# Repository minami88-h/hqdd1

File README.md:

# HQDD1 — 小型 QDD(準ダイレクトドライブ)アクチュエータ

ジンバルモーター(2204 / 260KV)+ 減速機を、自作の制御基板 **hqdd_1** で駆動する QDD アクチュエータの、基板設計・ファームウェア・操作用 Web UI をまとめたリポジトリです。

*A small quasi-direct-drive actuator: a custom STM32G431 + DRV8311H FOC driver board (KiCad files included), SimpleFOC-based firmware with CAN/UART control, and a browser UI (Web Serial / SocketCAN). Documentation is mostly in Japanese.*

| | |
|---|---|
| MCU | STM32G431KBUx(UFQFPN32、128 KB flash / 32 KB RAM) |
| モータードライバ | TI DRV8311H(3 × PWM、低サイド電流センス) |
| 角度センサー | AS5600L(I2C、12 bit) |
| CAN トランシーバ | TCAN330(FDCAN1、1 Mbps) |
| モーター | ジンバル 2204-260KV(極対数 7)、減速比 29.16 または 5.4 |
| 制御 | SimpleFOC による電流 FOC(トルク / 速度 / 位置モード) |
| 入力電圧 | LiPo バッテリー(2 セル直列 = 2S で動作確認)。3 セル直列(3S)は、UI で電源電圧を 12 V に設定すれば使える想定(実機では未確認) |

## 構成

```
hqdd1/
├── firmware/   PlatformIO プロジェクト(STM32G431 + SimpleFOC、CAN/UART 通信)
├── webui/      操作用 Web UI(ブラウザ + 任意のバックエンド server.py)
├── hardware/   KiCad プロジェクト(回路図・PCB・3D モデル・製造データ)
└── docs/       通信仕様書(Markdown / PDF)、アクチュエータの仕様サマリー
```

## 主な機能

- **電流 FOC** — トルク(電流)/ 速度 / 位置の 3 モード。モード切替時は目標を自動で安全な値にする(位置モードは現在位置で保持)。
- **CAN(FDCAN1)と UART の両方で制御** — 同じコマンド文字列を使います。CAN は最大 8 台を同一バスに接続でき、UART も `@<ID>` で宛先を指定できます。仕様は [docs/communication_spec.md](docs/communication_spec.md)([PDF](docs/communication_spec.pdf))。
- **パラメータの調整・保存** — PID ゲイン、電流/速度/電圧の上限、電源電圧、減速比を通信経由で変更でき、フラッシュに保存して電源を切っても保持。出荷状態(コード上の値)へ戻すコマンドもあります。
- **Web UI** — リアルタイムグラフ(項目を選んで増やせる)、運転操作、PID・制限値の調整、高速キャプチャ(ステップ応答の記録)。
- **ボタンとLED** — 基板上のボタンでデバイス ID を設定し、LED で ID と負荷を表示。

## はじめに

### 1. ファームウェアを書き込む

必要なもの: [PlatformIO](https://platformio.org/)、ST-Link(基板に ST-Link は載っていないので、J2 の SWDIO/SWCLK に外付けします)。

```bash
cd firmware
pio run                 # ビルド
pio run -t upload       # ST-Link で書き込み
```

> **新しい基板に初めて書き込むときは、先に下の「オプションバイトの修正」を一度だけ実行してください。** しないと、書き込みは成功しても毎回ブートローダに入り、動きません。

**書き込みの動作について。** ビルドごとに固有の番号を保存データに付けているため、**プログラムを書き込み直すと、保存済みのパラメータとデバイス ID はコード上の値に戻ります**。調整した値を残したい場合は、コードの初期値(`firmware/src/main.cpp`)に反映してから書き込んでください。ID の既定値は `firmware/src/device_id.h` の `DEFAULT_DEVICE_ID` です。

### 2. 配線

| 機能 | 内容 |
|---|---|
| 電源 | LiPo バッテリー。2 セル直列(2S、公称 7.4 V)で動作確認。UI の「電源電圧」を 2S = 8 V / 3S(3 セル直列、公称 11.1 V)= 12 V に合わせる。3S は実機未確認で、電源まわりの部品の耐圧は各自で確認すること |
| UART(J3) | USB-TTL アダプタの TXD → 基板 PA15、RXD → 基板 PA2、GND(3.3 V TTL、115200 bps) |
| CAN | CAN_H / CAN_L、バスの両端に 120 Ω の終端(1 Mbps) |
| 書き込み(J2) | ST-Link の SWDIO / SWCLK / GND |

### 3. Web UI を使う

**UART だけなら、サーバ不要でブラウザだけで使えます。** Chrome または Edge で UI を開き、「接続」を押してシリアルポートを選びます(Web Serial を使うため、Firefox / Safari は非対応)。

- 公開ページ: <https://minami88-h.github.io/hqdd1/>(GitHub Pages)
- ローカルで開く場合: `cd webui/static && python3 -m http.server 8099` → <http://localhost:8099>

**CAN を使う場合**は、PC 側のバックエンドが必要です(Linux の SocketCAN を使います)。

```bash
# CAN アダプタを can0 として立ち上げる(例: gs_usb 系)
sudo ip link set can0 up type can bitrate 1000000
# slcan ファームのアダプタの場合: sudo slcand -o -c -s8 /dev/ttyACM0 can0 && sudo ip link set can0 up

pip install aiohttp pyserial
python3 webui/server.py          # -> http://localhost:8080
```

UART もサーバ経由で使えます(UI のヘッダーで「経路」を切り替え)。

## 通信

CAN と UART の仕様(フレーム形式、コマンド一覧、パラメータ表、複数台の運用)は **[docs/communication_spec.md](docs/communication_spec.md)** にまとめています。簡単な例:

```bash
cansend can0 101#4D4331      # ID=1 に "MC1"(速度モード)
cansend can0 101#4D32        # "M2"(2 rad/s)
candump can0                 # 0x201 に 20 ms 周期でテレメトリ
```

```
@1 MC1                       # UART: ID=1 を速度モードに
@1 M2                        # 2 rad/s
@1 ?VP                       # -> #1 GAIN VP 0.03000
```

## ハードウェア

KiCad のプロジェクトは [hardware/](hardware/) にあります(KiCad 10 で保存。4 層基板)。製造用データ(ガーバー、BOM、実装位置)は `hardware/production/` です。詳しくは [hardware/README.md](hardware/README.md)。

### ピン対応

回路図(`hardware/mcu.kicad_sch`)から確定したものです。

| 機能 | MCU ピン | 備考 |
|---|---|---|
| PWM A/B/C → DRV8311 INHA/B/C | PA8 / PA9 / PA10 | TIM1 CH1/2/3 |
| DRV8311 nSLEEP(enable) | PB0 | アクティブ High |
| 電流センス SOA / SOB | PA0 / PA1 | ADC1。GAIN は 3.3 V 直結(2 V/A) |
| AS5600L I2C | SDA = PB7、SCL = PB8 | I2C1(AF4) |
| デバッグ UART(USART2) | TX = PA2、RX = PA15 | J3 |
| CAN(FDCAN1) | TX = PA12、RX = PA11 | TCAN330 経由 |
| SWD | PA13 / PA14 | J2 |
| LED0 / LED1 | PA4 / PA5 | 負荷検出 / ID 表示 |
| SET_ID(ボタン) | PA3 | 2 秒長押しで ID 設定モード |

回路図のネット名 `UART_TX` = PA15、`UART_RX` = PA2 は、外部機器から見た向きの名前です(MCU から見ると PA2 が送信、PA15 が受信)。**配線は回路図のラベル通り**(アダプタの TXD → `UART_TX`、RXD → `UART_RX`)で動作します。

## 重要な注意点

### オプションバイトの修正(チップごとに 1 回だけ)

STM32G431 は、出荷設定(`nSWBOOT0 = 1`)だと BOOT0 を **PB8 ピンの電圧**で判定します。この基板は PB8 を AS5600 の I2C SCL に使い、4.7 kΩ で 3.3 V にプルアップしているため、**リセットのたびに BOOT0 = High と判定され、毎回システムブートローダに入ってしまいます**(書き込み・ベリファイ自体は成功します)。`nSWBOOT0` をクリアして、常にメインフラッシュから起動するようにします。新品のチップ、または基板を新規製作したときに、ST-Link で 1 回だけ実行してください。

```bash
OOCD=~/.platformio/packages/tool-openocd/bin/openocd
SCRIPTS=~/.platformio/packages/tool-openocd/openocd/scripts
$OOCD -s $SCRIPTS -f interface/stlink.cfg -f target/stm32g4x.cfg \
  -c "init" -c "halt" \
  -c "stm32l4x option_write 0 0x20 0x00000000 0x04000000" \
  -c "stm32l4x option_load 0" \
  -c "shutdown"
```

`option_load` でリセットがかかるため "option load failed" と表示されることがありますが、正常です。設定はチップに恒久保存されます。

### デバッグ用シリアルのピン指定

`firmware/platformio.ini` で `PIN_SERIAL_TX=PA2_ALT1` を指定しています。素の `PA2` だと、STM32duino のピンマップ上で LPUART1 の TX に解決され、USART2 の RX(PA15)と食い違って `Serial` が応答しなくなります。

### 電源電圧の設定

基板には電源電圧を測る回路がありません。LiPo バッテリーを替えたら(2 セル = 2S ⇔ 3 セル = 3S)、UI の「電源電圧」を合わせてください(2S = 8 V、3S = 12 V)。ゲインの変更は不要です。合っていないと電流ループの実効ゲインがずれ、発振することがあります。

### 通信が途切れたときの動作

基板は通信断を検出して停止する機能を持ちません。最後に受けた指令のまま動き続けます。上位側で、定期的な送信と停止手順を用意してください。

## 既知の課題

- **TCAN330 の STANDBY(S)/SHDN ピン**が、基板パターンでは未接続です。現在の実機ではジャンパ線で対処しています(基板の修正が必要です)。
- **DRV8311 の AGND/PGND に接続されているネット名が `VDD`** になっています(`power.kicad_sch` の電源レールと同名)。GND であるべき箇所と思われますが、実害がないため未検証です。基板実体の配線を確認してください。
- CAN の受信はメインループ 1 周につき 1 フレームです(約 2 kHz)。連続して送る場合は 1 ms 以上の間隔を空けてください。

## ライセンス

**非商用であれば自由に使えます。商用利用は、著作権者以外には許可していません。**

| 対象 | ライセンス |
|---|---|
| ソフトウェア(`firmware/`、`webui/` など) | [PolyForm Noncommercial 1.0.0](LICENSES/PolyForm-Noncommercial-1.0.0.md) |
| ハードウェア設計・文書(`hardware/`、`docs/`) | [CC BY-NC 4.0](LICENSES/CC-BY-NC-4.0.txt) |
| `firmware/src/can_driver/` | [ACANFD_STM32](https://github.com/pierremolinaro/ACANFD_STM32)(MIT)。同ディレクトリの `LICENSE-ACANFD_STM32` |

個人・趣味・学習・教育・研究での利用や改変は自由です。商用利用を希望する場合は、[GitHub の Issues](https://github.com/minami88-h/hqdd1/issues) から連絡してください。詳しくは [LICENSE](LICENSE) を参照してください。ビルド時に取得される [SimpleFOC](https://simplefoc.com/) などのライブラリは、それぞれのライセンスに従います。

## 謝辞

[SimpleFOC](https://simplefoc.com/)、[ACANFD_STM32](https://github.com/pierremolinaro/ACANFD_STM32)

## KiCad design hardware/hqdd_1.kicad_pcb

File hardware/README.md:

# hqdd_1 基板(KiCad)

STM32G431KBUx + DRV8311H + AS5600L + TCAN330 の制御基板です。KiCad 10 で保存されています(4 層基板)。古い版では開けません。

## ファイル

| ファイル | 内容 |
|---|---|
| `hqdd_1.kicad_pro` | プロジェクト |
| `hqdd_1.kicad_sch` | ルートの回路図(`mcu` と `power` の 2 シートを持つ) |
| `mcu.kicad_sch` | MCU、DRV8311H、AS5600L、TCAN330、コネクタ類 |
| `power.kicad_sch` | 電源まわり |
| `hqdd_1.kicad_pcb` | PCB |
| `hqdd_1.step` | 3D モデル(PCB から出力) |
| `production/` | 製造用データ(下記) |
| `fabrication-toolkit-options.json` | Fabrication Toolkit(KiCad プラグイン)の出力設定 |

### `production/`

Fabrication Toolkit で出力した発注用データです。

| ファイル | 内容 |
|---|---|
| `hqdd_1.zip` | ガーバーとドリルデータ |
| `bom.csv` | 部品表 |
| `positions.csv` | 部品の実装位置 |
| `designators.csv` | リファレンス一覧 |
| `netlist.ipc` | IPC ネットリスト |

## 既知の課題

- TCAN330 の STANDBY(S)/SHDN ピンが基板パターンで未接続です(ジャンパ線で対処)。
- DRV8311 の AGND/PGND に接続されているネット名が `VDD` になっています。GND であるべき箇所と思われますが、未検証です。

回路の詳細、ピン対応、通信は、ルートの [README](../README.md) を参照してください。

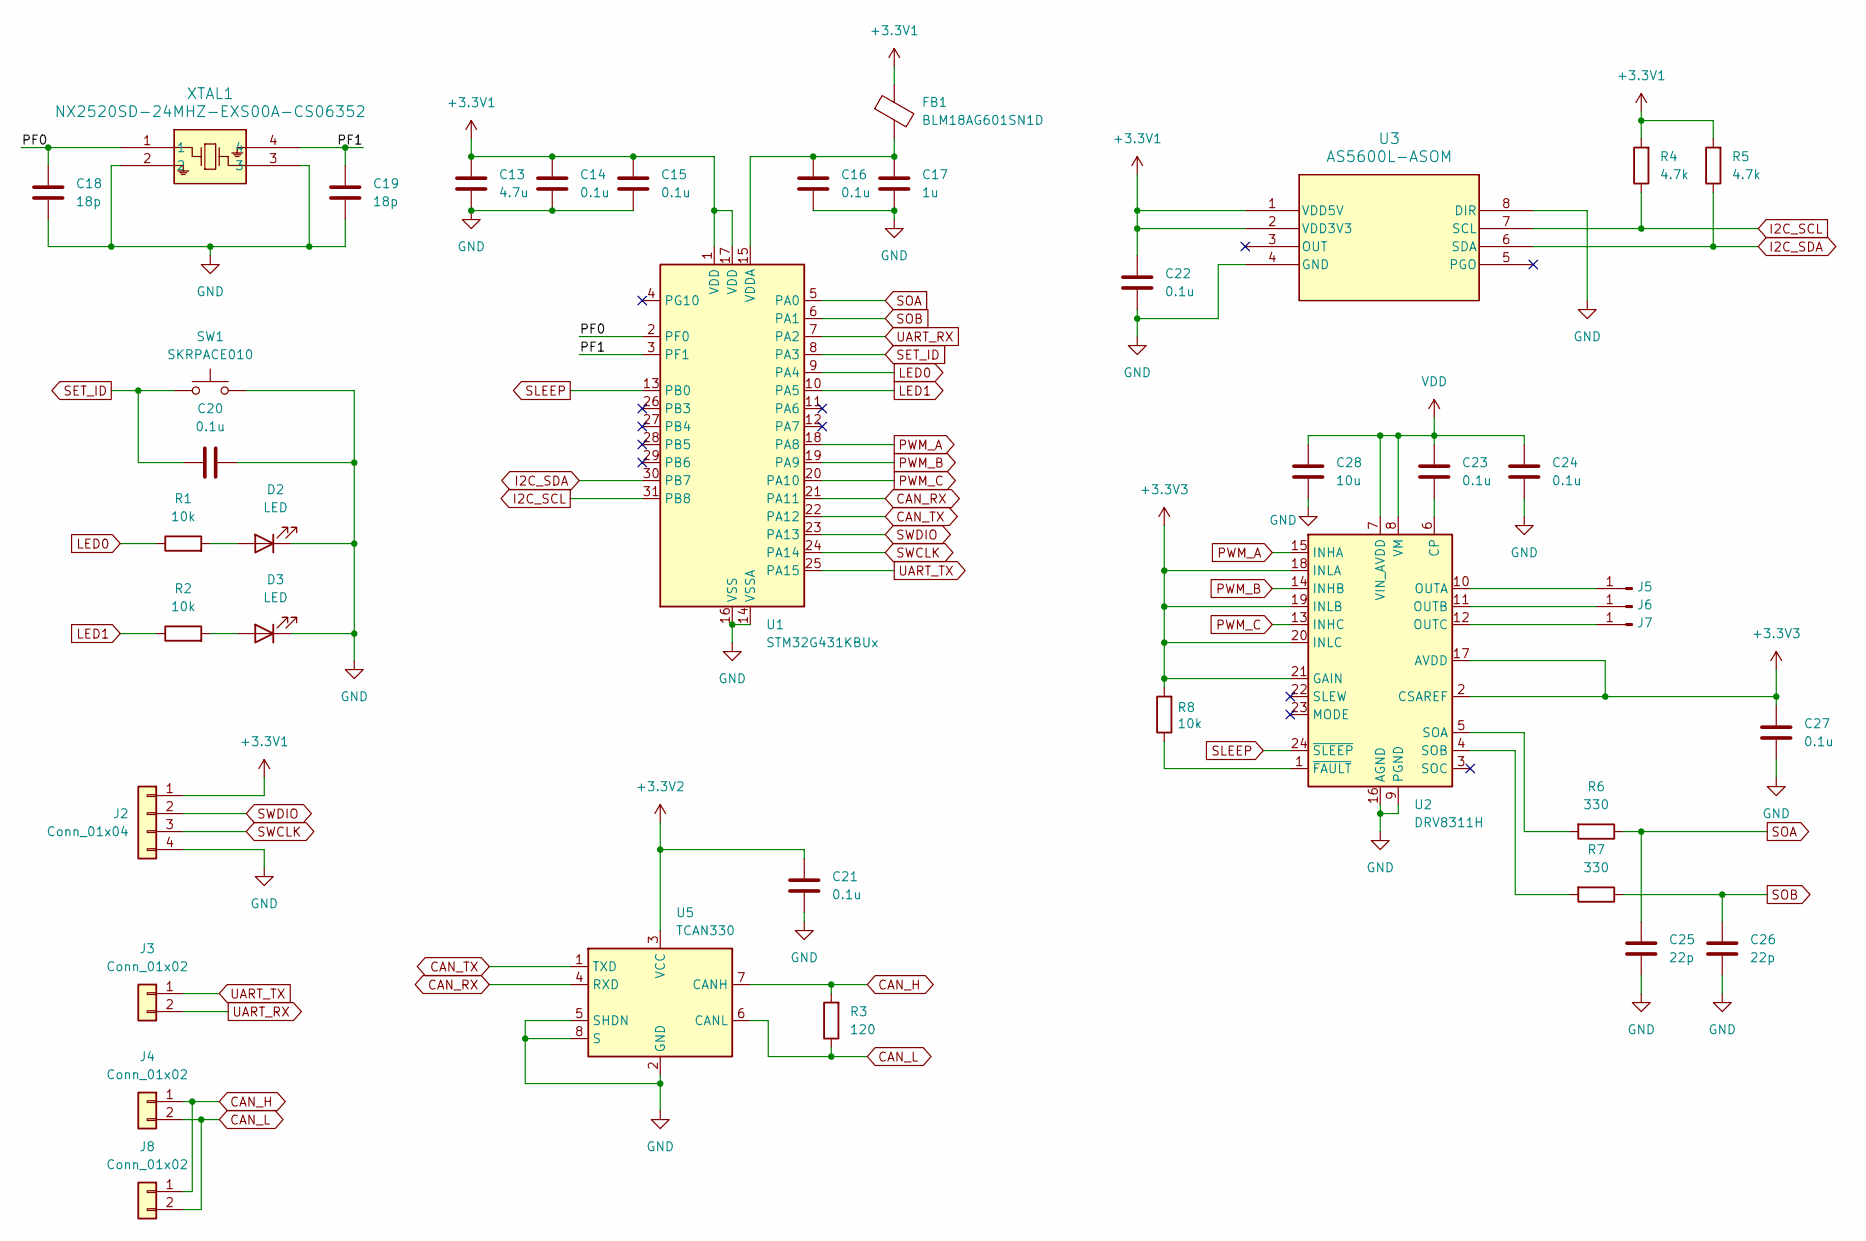
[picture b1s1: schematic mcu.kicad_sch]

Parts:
C13: 4.7u; C_0603_1608Metric_Pad1.08x0.95mm_HandSolder
C14, C15, C16, C20, C21, C22, C23, C24, C27: 0.1u; C_0603_1608Metric_Pad1.08x0.95mm_HandSolder
C17: 1u; C_0603_1608Metric_Pad1.08x0.95mm_HandSolder
C18, C19: 18p; C_0402_1005Metric_Pad0.74x0.62mm_HandSolder
C25, C26: 22p; C_0402_1005Metric_Pad0.74x0.62mm_HandSolder
C28: 10u; C_0603_1608Metric_Pad1.08x0.95mm_HandSolder
D2, D3: LED; LED_0603_1608Metric_Pad1.05x0.95mm_HandSolder
FB1: BLM18AG601SN1D; C_0603_1608Metric_Pad1.08x0.95mm_HandSolder
J2: Conn_01x04; JST_ZH_B4B-ZR_1x04_P1.50mm_Vertical
J3, J4, J8: Conn_01x02; JST_ZH_B2B-ZR_1x02_P1.50mm_Vertical
J5, J6, J7: Conn_01x01_Pin; pad
R1, R2, R8: 10k; R_0603_1608Metric_Pad0.98x0.95mm_HandSolder
R3: 120; R_0603_1608Metric_Pad0.98x0.95mm_HandSolder
R4, R5: 4.7k; R_0603_1608Metric_Pad0.98x0.95mm_HandSolder
R6, R7: 330; R_0603_1608Metric_Pad0.98x0.95mm_HandSolder
SW1: SKRPACE010; SW_SPST_PTS810
U1: STM32G431KBUx; QFN-32-1EP_5x5mm_P0.5mm_EP3.45x3.45mm
U2: DRV8311H; RRW0024-MFG
U3: AS5600L-ASOM; AS5600L-ASOM_AMS
U5: TCAN330; TSOT-23-8_HandSoldering
XTAL1: NX2520SD-24MHZ-EXS00A-CS06352; NX2520SD_NDK-L

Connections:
+3.3V1: C13.1, C14.1, C15.1, C22.1, FB1.1, J2.1, R4.2, R5.2, U1.1 (VDD), U1.17 (VDD), U3.1 (VDD5V), U3.2 (VDD3V3); also elsewhere on the board
+3.3V2: C21.1, U5.3 (VCC); also elsewhere on the board
+3.3V3: C27.1, R8.2, U2.2 (CSAREF), U2.17 (AVDD), U2.18 (INLA), U2.19 (INLB), U2.20 (INLC), U2.21 (GAIN)
/mcu/PF0: C18.1, U1.2 (PF0), XTAL1.1
/mcu/PF1: C19.1, U1.3 (PF1), XTAL1.4
CAN_H: J4.1, J8.1, R3.2, U5.7 (CANH)
CAN_L: J4.2, J8.2, R3.1, U5.6 (CANL)
CAN_RX: U1.21 (PA11), U5.4 (RXD)
CAN_TX: U1.22 (PA12), U5.1 (TXD)
GND: C13.2, C14.2, C15.2, C16.2, C17.2, C18.2, C19.2, C20.2, C21.2, C22.2, C24.2, C25.2, C26.2, C27.2, C28.2, D2.1 (K), D3.1 (K), J2.4, SW1.2, U1.14 (VSSA), U1.16 (VSS), U1.32 (VSS), U1.33 (VSS), U2.9 (PGND), U2.16 (AGND), U2.25 (PGND), U2.26, U2.27, U2.28, U2.29, U2.30, U3.4 (GND), U3.8 (DIR), U5.2 (GND), U5.5 (SHDN), U5.8 (S), XTAL1.2, XTAL1.3; also elsewhere on the board
I2C_SCL: R4.1, U1.31 (PB8), U3.7 (SCL)
I2C_SDA: R5.1, U1.30 (PB7), U3.6 (SDA)
LED0: R1.1, U1.9 (PA4)
LED1: R2.1, U1.10 (PA5)
unnamed: D2.2 (A), R1.2
unnamed: D3.2 (A), R2.2
unnamed: J5.1 (Pin_1_1), U2.10 (OUTA)
unnamed: J6.1 (Pin_1_1), U2.11 (OUTB)
unnamed: J7.1 (Pin_1_1), U2.12 (OUTC)
unnamed: C16.1, C17.1, FB1.2, U1.15 (VDDA)
unnamed: C23.2, U2.6 (CP)
unnamed: R6.2, U2.5 (SOA)
unnamed: R7.2, U2.4 (SOB)
unnamed: R8.1, U2.1 (~FAULT)
PWM_A: U1.18 (PA8), U2.15 (INHA)
PWM_B: U1.19 (PA9), U2.14 (INHB)
PWM_C: U1.20 (PA10), U2.13 (INHC)
SET_ID: C20.1, SW1.1, U1.8 (PA3)
SLEEP: U1.13 (PB0), U2.24 (~SLEEP)
SOA: C25.1, R6.1, U1.5 (PA0)
SOB: C26.1, R7.1, U1.6 (PA1)
SWCLK: J2.3, U1.24 (PA14)
SWDIO: J2.2, U1.23 (PA13)
UART_RX: J3.2, U1.7 (PA2)
UART_TX: J3.1, U1.25 (PA15)
VDD: C23.1, C24.1, C28.1, U2.7 (VIN_AVDD), U2.8 (VM); also elsewhere on the board

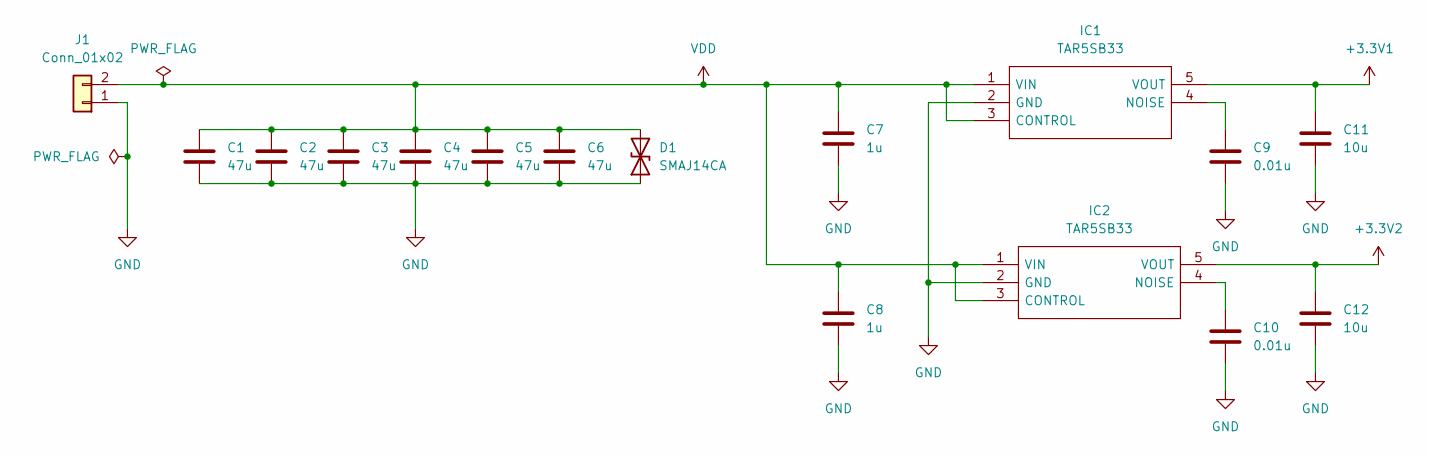
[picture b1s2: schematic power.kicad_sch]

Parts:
C1, C2, C3, C4, C5, C6: 47u; C_1206_3216Metric_Pad1.33x1.80mm_HandSolder
C7, C8: 1u; C_0603_1608Metric_Pad1.08x0.95mm_HandSolder
C9, C10: 0.01u; C_0402_1005Metric_Pad0.74x0.62mm_HandSolder
C11, C12: 10u; C_0603_1608Metric_Pad1.08x0.95mm_HandSolder
D1: SMAJ14CA; SMASeries_LTF
IC1, IC2: TAR5SB33; TA75S558FLF; Manufacturer_Part_Number TAR5SB33
J1: Conn_01x02; AMASS_XT30UPB-M_1x02_P5.0mm_Vertical

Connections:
+3.3V1: C11.1, IC1.5 (VOUT); also elsewhere on the board
+3.3V2: C12.1, IC2.5 (VOUT); also elsewhere on the board
GND: C1.2, C2.2, C3.2, C4.2, C5.2, C6.2, C7.2, C8.2, C9.2, C10.2, C11.2, C12.2, D1.1 (A1), IC1.2 (GND), IC2.2 (GND), J1.1; also elsewhere on the board
unnamed: C9.1, IC1.4 (NOISE)
unnamed: C10.1, IC2.4 (NOISE)
VDD: C1.1, C2.1, C3.1, C4.1, C5.1, C6.1, C7.1, C8.1, D1.2 (A2), IC1.1 (VIN), IC1.3 (CONTROL), IC2.1 (VIN), IC2.3 (CONTROL), J1.2; also elsewhere on the board

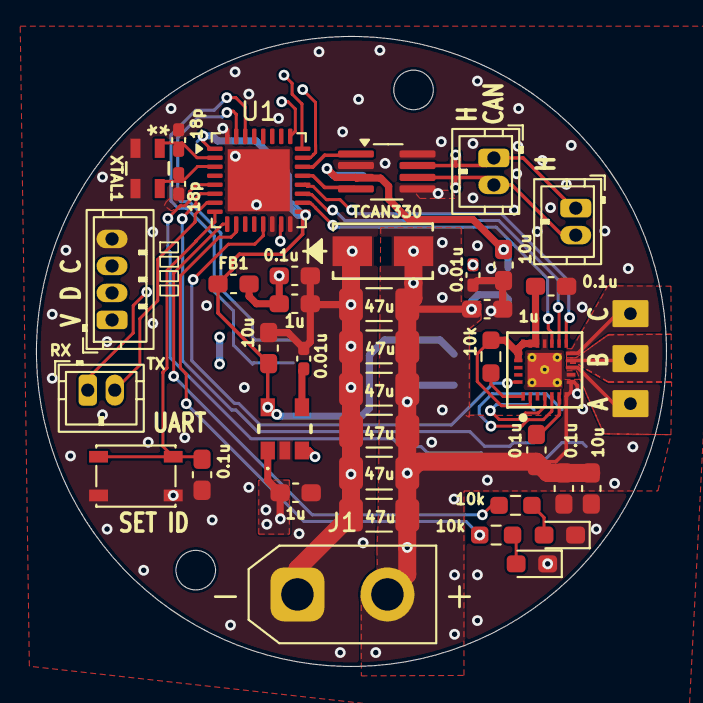
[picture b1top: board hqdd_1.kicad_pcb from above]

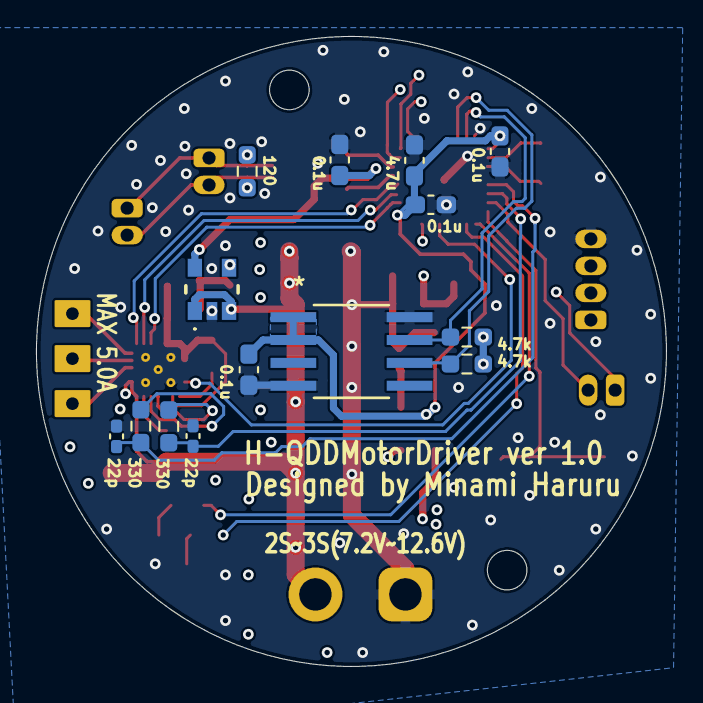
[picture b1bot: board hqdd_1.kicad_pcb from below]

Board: 4 copper layers, 35.0 x 35.0 mm, 56 parts (14 on the bottom side), 38 nets.

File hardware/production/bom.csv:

Designator,Footprint,Quantity,Value,LCSC Part #
"C1, C2, C3, C4, C5, C6",1206,6,47u,
"C10, C9",0402,2,0.01u,
"C11, C12, C28",0603,3,10u,
C13,0603,1,4.7u,
"C14, C15, C16, C20, C21, C22, C23, C24, C27",0603,9,0.1u,
"C17, C7, C8",0603,3,1u,
"C18, C19",0402,2,18p,
"C25, C26",0402,2,22p,
D1,SMASeries_LTF,1,SMAJ14CA,
"D2, D3",0603,2,LED,
FB1,0603,1,BLM18AG601SN1D,
"IC1, IC2",TA75S558FLF,2,TAR5SB33,
J1,AMASS_XT30UPB-M_1x02_P5.0mm_Vertical,1,Conn_01x02,
J2,JST_ZH_B4B-ZR_1x04_P1.50mm_Vertical,1,Conn_01x04,
"J3, J4, J8",JST_ZH_B2B-ZR_1x02_P1.50mm_Vertical,3,Conn_01x02,
"J5, J6, J7",pad,3,Conn_01x01_Pin,
"R1, R2, R8",0603,3,10k,
R3,0603,1,120,
"R4, R5",0603,2,4.7k,
"R6, R7",0603,2,330,
SW1,SW_SPST_PTS810,1,SKRPACE010,
U1,QFN-32-1EP_5x5mm_P0.5mm_EP3.45x3.45mm,1,STM32G431KBUx,
U2,RRW0024-MFG,1,DRV8311H,
U3,AS5600L-ASOM_AMS,1,AS5600L-ASOM,
U5,TSOT-23-8_HandSoldering,1,TCAN330,
XTAL1,NX2520SD_NDK-L,1,NX2520SD-24MHZ-EXS00A-CS06352,

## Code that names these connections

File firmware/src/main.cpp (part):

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 *  ピン配置とボード固有の初期化(Serial)のみ。
 *
 *  ---- ピン対応 (hardware/mcu.kicad_sch から実機配線を解析して確定) ----
 *    DRV8311 INHA/INHB/INHC <- PA8/PA9/PA10 (TIM1, 低サイドCS同期に必須)
 *    DRV8311 nSLEEP         <- PB0  (enable, アクティブHigh)
 *    DRV8311 SOA/SOB        -> PA0/PA1 (ADC1_IN1/IN2, 電流センス)
 *    DRV8311 GAIN            = +3.3V 直結 (2V/A)  -> CSENSE_VpA=2.0
 *    DRV8311 INLA/INLB/INLC  = +3.3V 直結 (3xPWMモードの定石通り)
 *    DRV8311 MODE            = NC (Hi-Z, 9A OCP)
 *    AS5600L SDA/SCL        <- PB7/PB8 (I2C1, AF4)
 *    SWDIO/SWCLK            <- PA13/PA14 (J2, 外付けST-Linkで書き込み)
 *    デバッグSerial(USART2)  : TX=PA2 / RX=PA15 (J3, 外付けUSB-TTL)
 *      ※回路図のネット名は "UART_RX"=PA2 / "UART_TX"=PA15 (外部機器視点の
 *        命名)。MCUのハードウェアUSART2としてはPA2=TX/PA15=RXでないと
 *        動かない。USB-TTLアダプタの TXD を基板PA2に、RXDを基板PA15に
 *        接続すること。(platformio.iniでPIN_SERIAL_TX/RXを固定済み)
 *
 *  ---- CAN通信(FDCAN1) / ボタンID / 負荷LED ----
 *    CAN (FDCAN1)  : TX=PA12 / RX=PA11 (TCAN330経由、1Mbps)
 *      TCAN330のSTANDBY(S)/SHDNピンはジャンパ線で解決済み。
 *      受信ID=0x100+id、送信(テレメトリ)ID=0x200+id。詳細はcan_link.h/.cpp。
 *    SET_ID(押しボタン)=PA3 : 2秒長押しでID変更モード、押下回数(1〜8)で
 *      id=回数-1を確定・フラッシュ保存。詳細はui.h/.cpp、device_id.h/.cpp。
 *    LED1=PA5 : 現在IDを(id+1)回点滅で表示。LED0=PA4 : 負荷検出(|Iq|閾値)。
 * ============================================================ */
#include <SimpleFOC.h>
#include "device_id.h"
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#define CURRENT_LIMIT   1.0f     // [A]
#define CSENSE_VpA      2.0f     // GAIN=AVDD相当(+3.3V直結) -> 2 V/A

TwoWire I2Cbus = TwoWire(PB7, PB8);
MagneticSensorI2C sensor = MagneticSensorI2C(AS5600_I2C);
BLDCDriver3PWM driver = BLDCDriver3PWM(PA8, PA9, PA10, PB0);
LowsideCurrentSense currentSense = LowsideCurrentSense(CSENSE_VpA, 1.0f, PA0, PA1);
BLDCMotor motor = BLDCMotor(POLE_PAIRS);

Commander command = Commander(Serial);
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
